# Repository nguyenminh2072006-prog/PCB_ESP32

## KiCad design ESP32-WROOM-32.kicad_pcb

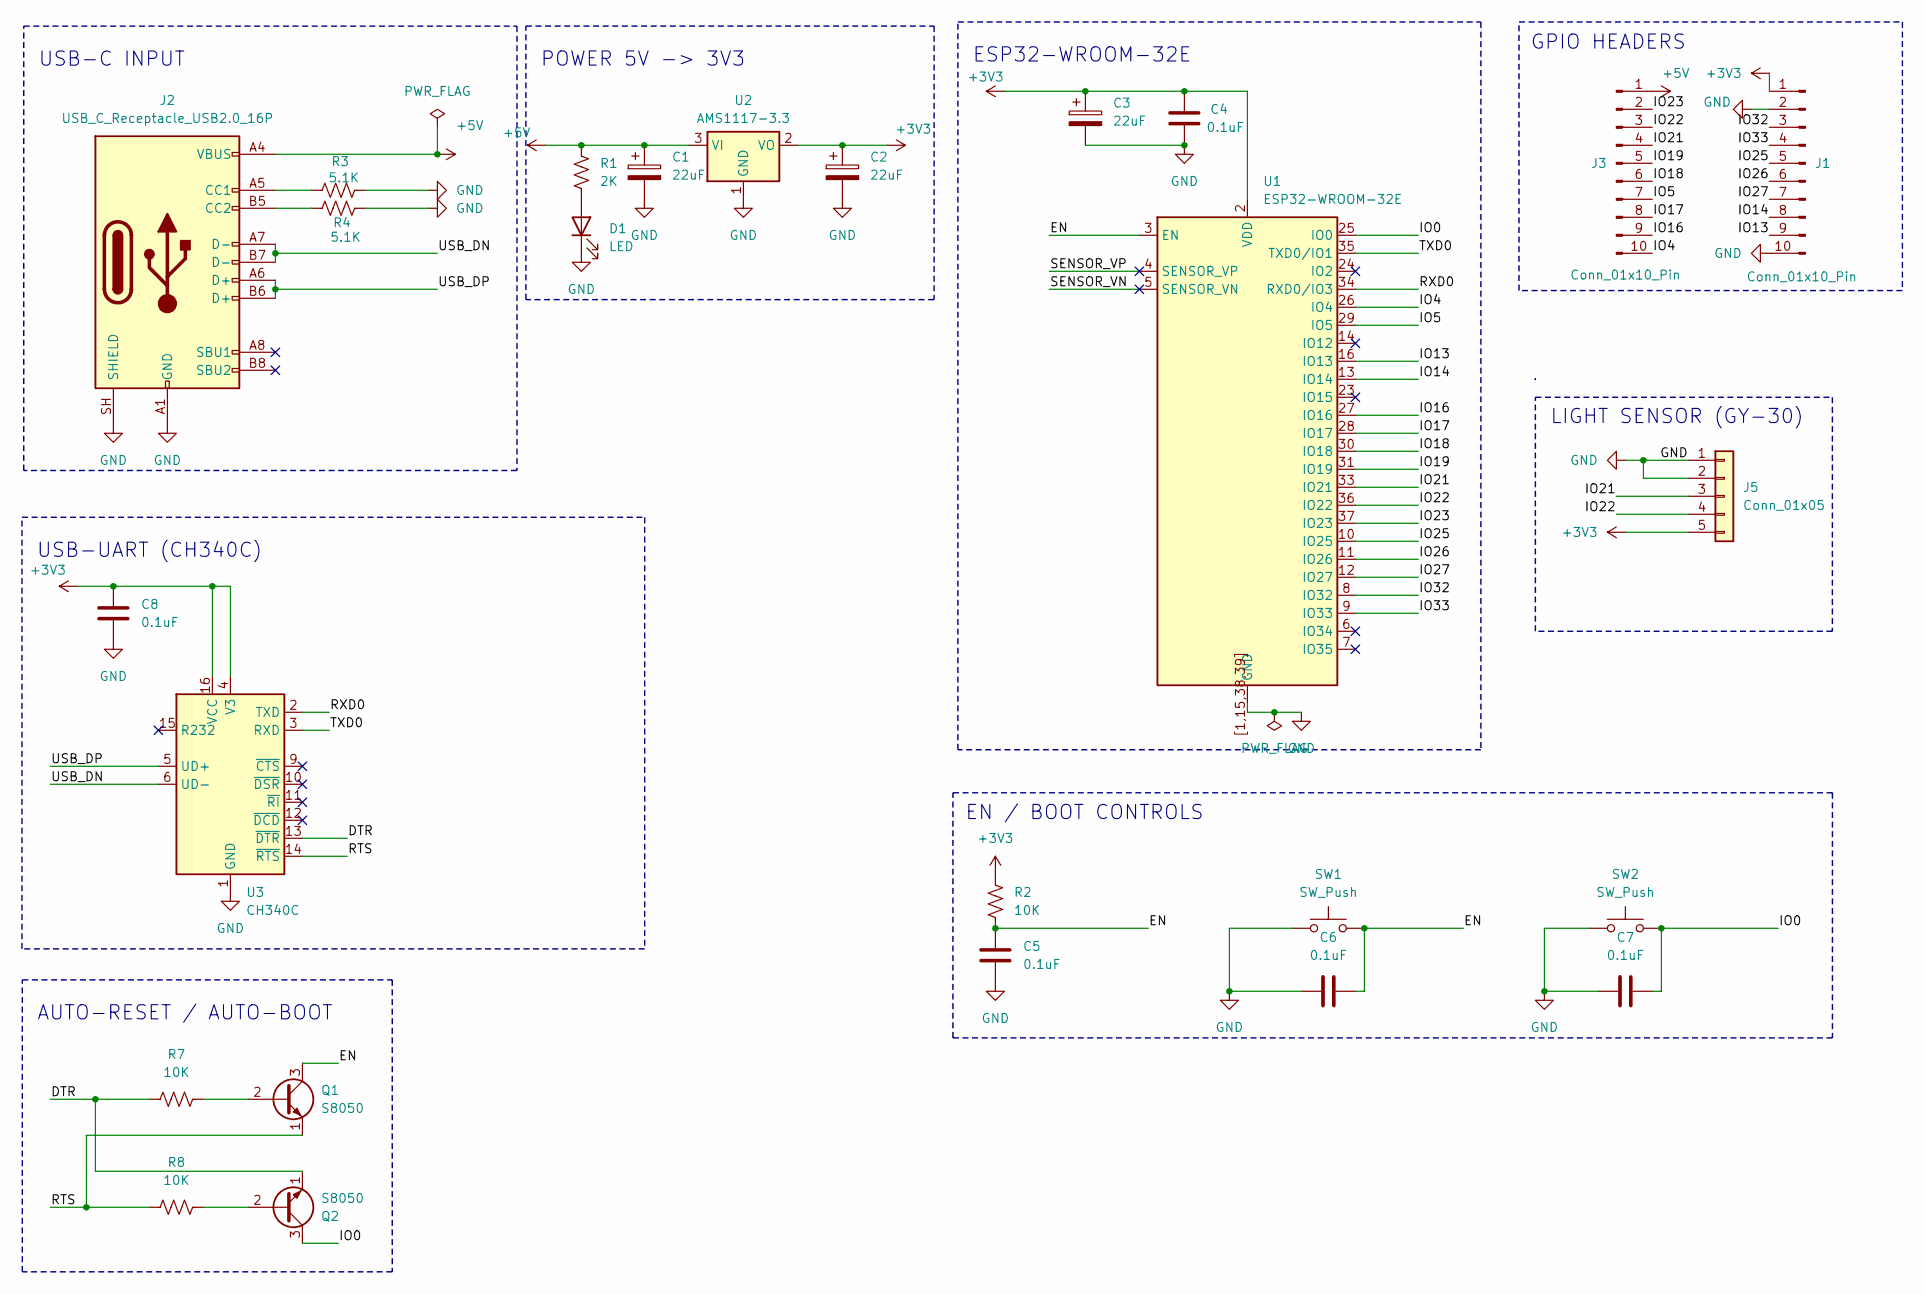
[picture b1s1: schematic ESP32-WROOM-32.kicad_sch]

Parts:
C1, C2, C3: 22uF; CP_Radial_D5.0mm_P2.00mm
C4, C5, C6, C7, C8: 0.1uF; C_Disc_D3.0mm_W1.6mm_P2.50mm
D1: LED; LED_D3.0mm
J1, J3: Conn_01x10_Pin; PinHeader_1x10_P2.54mm_Vertical
J2: USB_C_Receptacle_USB2.0_16P; USB_C_Receptacle_GCT_USB4105-xx-A_16P_TopMnt_Horizontal
J5: Conn_01x05; PinSocket_1x05_P2.54mm_Vertical
Q1, Q2: S8050; TO-92_Inline
R1: 2K; R_Axial_DIN0207_L6.3mm_D2.5mm_P7.62mm_Horizontal
R2, R7, R8: 10K; R_Axial_DIN0207_L6.3mm_D2.5mm_P7.62mm_Horizontal
R3, R4: 5.1K; R_Axial_DIN0207_L6.3mm_D2.5mm_P7.62mm_Horizontal
SW1, SW2: SW_Push; SW_PUSH_6mm
U1: ESP32-WROOM-32E
U2: AMS1117-3.3; SOT-223-3_TabPin2
U3: CH340C; SOIC-16_3.9x9.9mm_P1.27mm

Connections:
+3V3: C2.1, C3.1, C4.1, C8.1, J1.1, J5.5, R2.1, U1.2 (VDD), U2.2 (VO), U3.4 (V3), U3.16 (VCC)
+5V: C1.1, J2.A4 (VBUS), J2.A9 (VBUS), J2.B4 (VBUS), J2.B9 (VBUS), J3.1, R1.1, U2.3 (VI)
/DTR: Q2.1 (E), R7.1, U3.13 (~DTR)
/EN: C5.1, C6.2, Q1.3 (C), R2.2, SW1.2, U1.3 (EN)
/IO0: C7.2, Q2.3 (C), SW2.2, U1.25 (IO0)
/IO4: J3.10, U1.26 (IO4)
/IO5: J3.7, U1.29 (IO5)
/IO13: J1.9, U1.16 (IO13)
/IO14: J1.8, U1.13 (IO14)
/IO16: J3.9, U1.27 (IO16)
/IO17: J3.8, U1.28 (IO17)
/IO18: J3.6, U1.30 (IO18)
/IO19: J3.5, U1.31 (IO19)
/IO21: J3.4, J5.3, U1.33 (IO21)
/IO22: J3.3, J5.4, U1.36 (IO22)
/IO23: J3.2, U1.37 (IO23)
/IO25: J1.5, U1.10 (IO25)
/IO26: J1.6, U1.11 (IO26)
/IO27: J1.7, U1.12 (IO27)
/IO32: J1.3, U1.8 (IO32)
/IO33: J1.4, U1.9 (IO33)
/RTS: Q1.1 (E), R8.1, U3.14 (~RTS)
/RXD0: U1.34 (RXD0/IO3), U3.2 (TXD)
/SENSOR_VN: U1.5 (SENSOR_VN)
/SENSOR_VP: U1.4 (SENSOR_VP)
/TXD0: U1.35 (TXD0/IO1), U3.3 (RXD)
/USB_DN: J2.A7 (D-), J2.B7 (D-), U3.6 (UD-)
/USB_DP: J2.A6 (D+), J2.B6 (D+), U3.5 (UD+)
GND: C1.2, C2.2, C3.2, C4.2, C5.2, C6.1, C7.1, C8.2, D1.1 (K), J1.2, J1.10, J2.A1 (GND), J2.A12 (GND), J2.B1 (GND), J2.B12 (GND), J2.SH (SHIELD), J5.1, J5.2, R3.2, R4.2, SW1.1, SW2.1, U1.1 (GND), U1.15 (GND), U1.38 (GND), U1.39 (GND), U1.[1,15,38,39] (GND), U2.1 (GND), U3.1 (GND)
unnamed: D1.2 (A), R1.2
unnamed: J2.A5 (CC1), R3.1
unnamed: J2.B5 (CC2), R4.1
unnamed: Q1.2 (B), R7.2
unnamed: Q2.2 (B), R8.2

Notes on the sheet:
EN / BOOT CONTROLS
LIGHT SENSOR (GY-30)
USB-C INPUT
AUTO-RESET / AUTO-BOOT
POWER 5V -> 3V3
ESP32-WROOM-32E
GPIO HEADERS
USB-UART (CH340C)

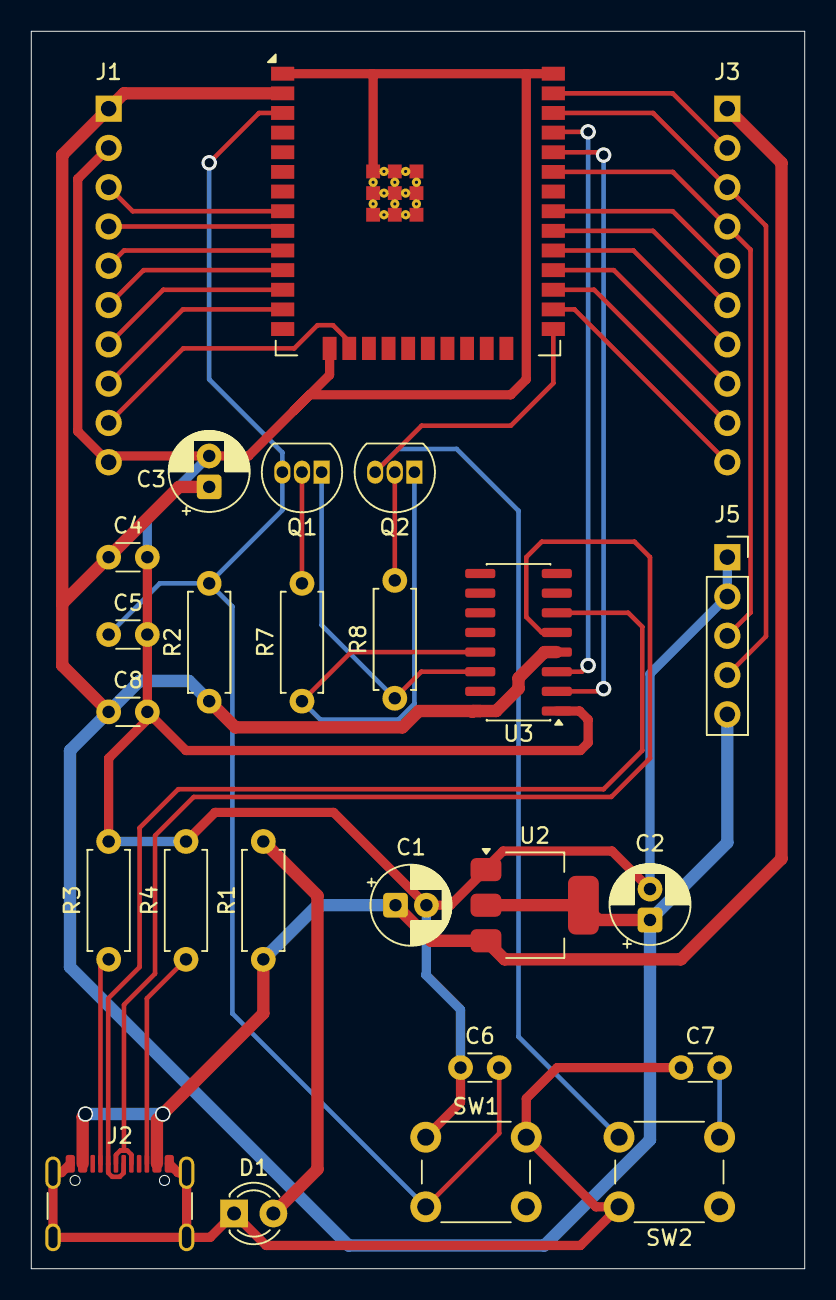
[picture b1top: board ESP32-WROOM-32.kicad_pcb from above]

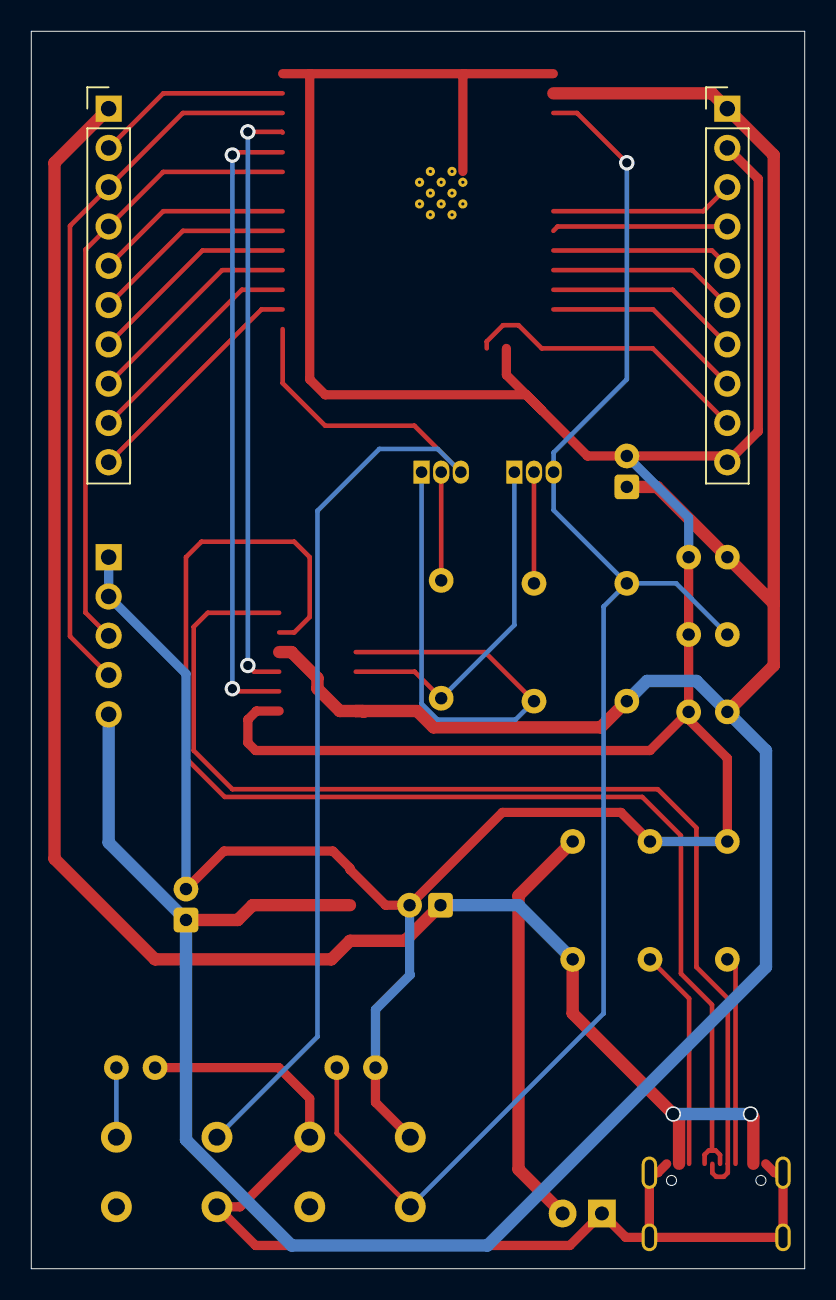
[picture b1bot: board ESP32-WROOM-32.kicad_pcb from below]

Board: 2 copper layers, 50.0 x 80.0 mm, 26 parts (2 on the bottom side), 32 nets.
